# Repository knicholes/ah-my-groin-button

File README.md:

# Ah! My Groin!

A big red arcade button in a 3D-printed box. Hit it, it plays a sound clip,
then it goes back to sleep drawing 150 µA — so a set of AA cells lasts months
rather than days.

This repo is the complete build: PCB design files, firmware, the parametric
case model, a bill of materials with the exact parts used, and a
step-by-step assembly guide written for someone who has not done much
soldering.

---

## What to build

Two things have version numbers and they move independently:

| | Current | Where |
|---|---|---|
| **Board** | v3.2 | `kicad/` |
| **Case** | v2 — 120 × 120 × 140 mm | `case/v2-120x120x140/` |

Everything else in the repo (`ah-my-groin/`, `v2/README.md`'s v1 comparisons,
`case/v1-200x130x110/`) is earlier work kept for reference. You do not need it.

### Honest status

Read this before you spend money.

| Part | State |
|---|---|
| Firmware | **Proven.** Runs on a physically built board. 0.15 mA idle measured 2026-07-25. |
| Power design | **Proven.** The phantom-power drain that made an earlier build useless was found and fixed; idle went 14.44 mA → 0.15 mA. |
| v3.2 PCB | **Designed, not yet fabricated.** Passes `kicad/verify_v3.py`. Nobody has held one of these boards. |
| v2 case | **Designed, not yet printed.** Passes its clearance checks. Nobody has printed one. |

So: the electronics are known to work, but *this specific board revision and
this specific case* are unbuilt. If you build first, you are the pilot. The
verification scripts below exist precisely because earlier revisions shipped
with bugs that KiCad's own DRC passed cleanly.

---

## Specifications

| | |
|---|---|
| Idle current | ~150 µA (0.15 mA measured) |
| Playback current | ~150 mA |
| Power | 3 × AA, 2.4–3.3 V, master switch on the holder |
| Response | ~1 s from press to audio (the audio module's genuine cold-boot time) |
| Audio | DY-SV17F, 4 MB onboard flash, no SD card |
| MCU | Pro Mini 3.3 V / 8 MHz, deep sleep + INT0 wake |
| Board | 90 × 70 mm, 2.0 mm FR4, 2-layer |
| Case | 120 × 120 × 140 mm, all corners and edges rounded |
| Cost | roughly $60–90 depending on what you already own |

---

## Build it

Six stages. Each one points at the document that is authoritative for it —
this README only orients you.

### 1. Order the parts

**[`v2/bom.md`](v2/bom.md)** lists every component with the exact ASIN that
was purchased, plus what each one is for and which ones have gotchas (the Pro
Mini crystal must read 8.000, not 16.000).

### 2. Order the PCB

Gerbers come from `kicad/`. Send to JLCPCB or equivalent: **2 layers,
2.0 mm thickness** (not the default 1.6 — the extra stiffness is deliberate,
an earlier unit failed by flexing on impact).

**Before you order, run the two gates:**

```
"K:\Program Files\KiCad\10.0\bin\python.exe" kicad\verify_v3.py   # must print PASS
"K:\Program Files\KiCad\10.0\bin\python.exe" kicad\fitcheck_v3.py # then print it at 100%
```

`verify_v3.py` checks two classes of bug KiCad's DRC structurally cannot see:
parts buried under a module's overhanging body, and electrical intent
(transistor orientation, pull-downs, the phantom-power split). Every board
revision so far shipped with at least one of these and a clean DRC.

`fitcheck_v3.py` produces a 1:1 sheet. Print it at 100 %, **check the two
100 mm calibration bars with a ruler**, then lay the real DY-SV17F and Pro
Mini on their footprints. This takes five minutes and is the only thing that
catches a wrong footprint pitch. The calibration bars are there because a
printer once silently rescaled the sheet and produced a convincing false
alarm.

### 3. Solder the board

**[`SOLDERING_GUIDE.md`](SOLDERING_GUIDE.md)** — the long one. Twelve steps
from bare PCB to finished unit, written for a beginner: which end of the
resistor, how to hold the iron, how to put a multimeter in series without
shorting the battery pack. It includes the continuity checks to run before
first power-on and the measurements that prove the power design is working.

No wires are soldered anywhere. Every connection is a PCB trace — that was
the entire point of the v3.2 respin.

### 4. Flash the firmware

```
cd v2/firmware
pio run              # build
pio run -t upload    # upload via FTDI cable on the 6-pin header
pio device monitor   # 9600 baud
```

[PlatformIO](https://platformio.org/) handles the toolchain. The firmware is
~60 lines with no libraries — the audio module is driven by one GPIO pulse.
See [`v2/firmware/main.cpp`](v2/firmware/main.cpp); its header comment
documents the pin map and, more usefully, *why* three of the pins are the way
they are. Those three comments are each a bug that cost a debugging session.

### 5. Load the audio

The DY-SV17F appears as a USB mass-storage device. Copy a single MP3 named
`00001.mp3` to it. That is all.

**This repo ships no audio files.** The clip the project is named after is
copyrighted, so supply your own — record something, or use a clip you have
the right to use. Any MP3 works.

### 6. Print and assemble the case

STLs are in **[`case/v2-120x120x140/`](case/v2-120x120x140/)**, and that
folder's `README.md` has per-part print orientations and the constraints that
shaped the design. Three parts: `body.stl` ×1, `bottom.stl` ×1, `foot.stl`
**×4**.

0.4 mm nozzle, 0.2 mm layer, 20 % infill, PLA or PETG. **Check the size your
slicer reports** — `body.stl` must load as 120 × 120 × 140 mm.

Assembly is Step 12 of the soldering guide. Order matters: the speaker's
screws become unreachable once the PCB is mounted.

---

## Repo map

```
README.md              you are here
SOLDERING_GUIDE.md     the build, end to end — the main document
PINOUTS.md             pin and net reference for the board
PLANS.md               the format the guide is written in

kicad/                 v3.2 board — schematic, layout, gerbers
    build_v3.py        generates the board from source
    verify_v3.py       pre-fabrication gate — must PASS before ordering
    fitcheck_v3.py     generates the 1:1 footprint check sheet

v2/
    bom.md             bill of materials — the source of truth for parts
    README.md          why v2's architecture replaced v1's
    firmware/          PlatformIO project; main.cpp is the whole program

case/
    build_v2.py        generates the current case
    render_v2.py       preview renders
    v2-120x120x140/    STLs to print, plus README with print orientations
    build_case.py      generates the older wide case
    v1-200x130x110/    superseded, kept so it still reproduces

ah-my-groin/           v1 firmware (DFPlayer + SD card). Superseded.
```

## Regenerating things

Both the board and the case are generated from scripts, not hand-drawn — so
if you change a dimension, re-run the script rather than editing the output.

```
"K:\Program Files\KiCad\10.0\bin\python.exe" kicad\build_v3.py
"K:\...\blender.exe" --background --python case\build_v2.py
```

The case script refuses to finish if its clearance checks fail, if the button
notches got filled back in by a later boolean, or if the exported STL is not
in millimetres. All three of those are real bugs that happened and shipped
silently.

## Building a different case

Change `W, D, H` and `VERSION` at the top of `case/build_v2.py` and re-run —
outputs land in a new `case/<VERSION>/` folder and the old one is untouched.
The clearance checks will tell you what stopped fitting. Three constraints
are worth knowing before you start, all documented in the v2 case README:
the PCB cannot sit on posts rising straight from the tray, everything
tray-mounted has to pass up through the bottom opening, and the top rim
rounding is what limits the button flange.

## Contributing

Issues and pull requests welcome. If you build one, the most useful thing you
can report is anything in the "not yet fabricated / not yet printed" rows
above turning out wrong.

## License

MIT — see [`LICENSE`](LICENSE). Build it, sell it, modify it, no permission
needed; just keep the copyright notice.

That covers everything in this repo: firmware, the board design, the case
models, and the documentation. It does **not** cover any audio you load onto
the device — no audio ships here, and whatever you add is yours to clear.

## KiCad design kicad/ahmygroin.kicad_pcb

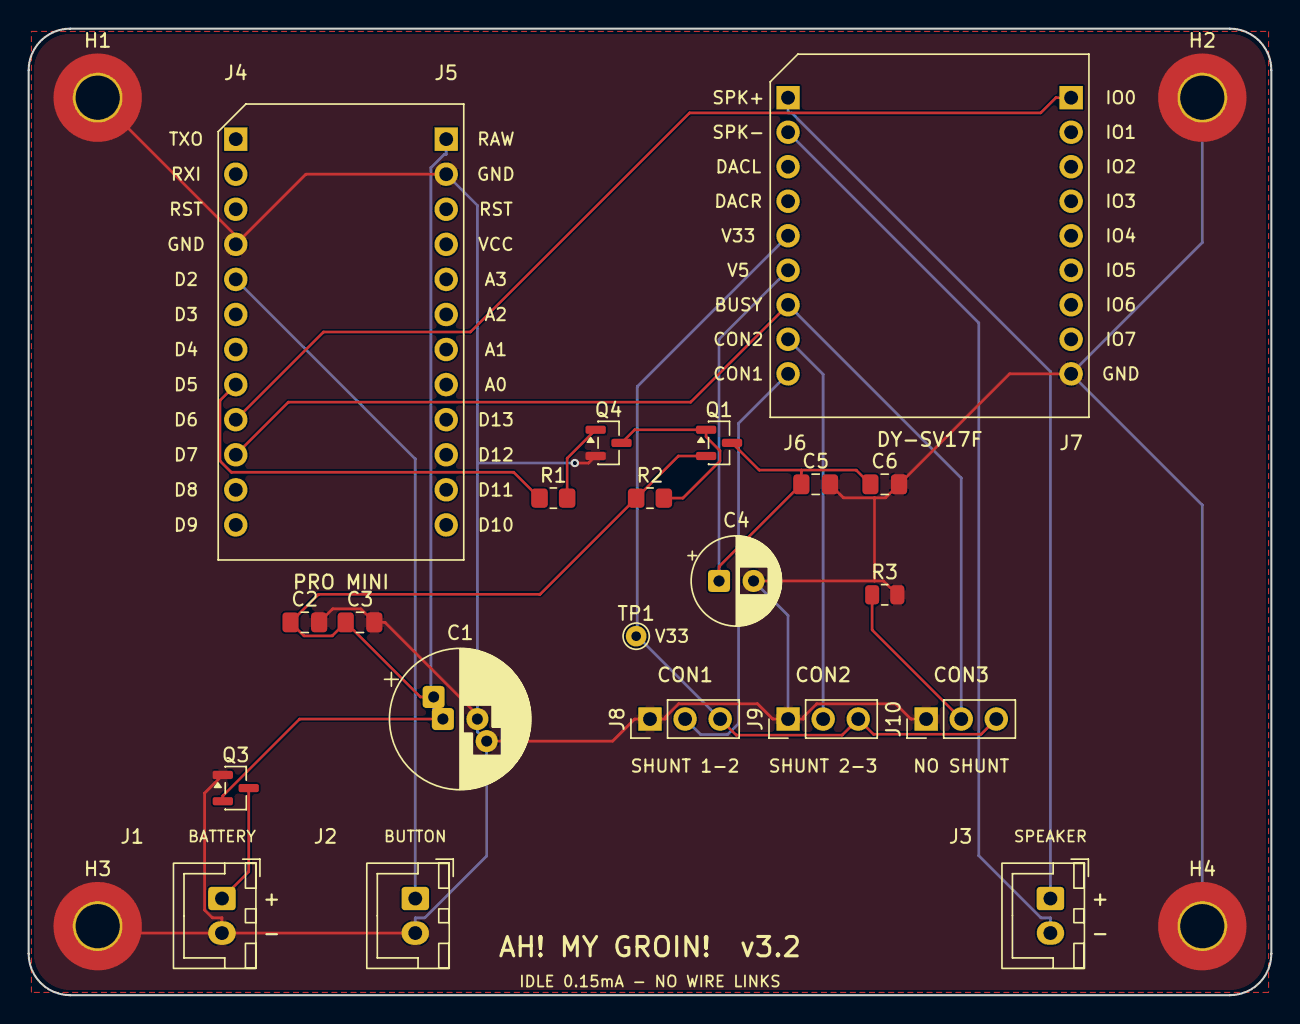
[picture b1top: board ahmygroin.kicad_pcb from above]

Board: 2 copper layers, 90.0 x 70.0 mm, 27 parts (0 on the bottom side), 15 nets.

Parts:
C1: 1000uF; CP_Radial_D10.0mm_P2.50mm_P5.00mm
C2, C6: 10uF; C_0805_2012Metric_Pad1.18x1.45mm_HandSolder
C3, C5: 0.1uF; C_0805_2012Metric_Pad1.18x1.45mm_HandSolder
C4: 100uF; CP_Radial_D6.3mm_P2.50mm
H1, H2, H3, H4: MountingHole; MountingHole_3.2mm_M3_Pad_TopBottom
J1: BAT; JST_XH_B2B-XH-A_1x02_P2.50mm_Vertical
J2: BTN; JST_XH_B2B-XH-A_1x02_P2.50mm_Vertical
J3: SPK; JST_XH_B2B-XH-A_1x02_P2.50mm_Vertical
J4: PROMINI_L; PinHeader_1x12_P2.54mm_Vertical
J5: PROMINI_R; PinHeader_1x12_P2.54mm_Vertical
J6: SV17F_IO; PinHeader_1x09_P2.54mm_Vertical
J7: SV17F_PWR; PinHeader_1x09_P2.54mm_Vertical
J8: MODE_CON1; PinHeader_1x03_P2.54mm_Vertical
J9: MODE_CON2; PinHeader_1x03_P2.54mm_Vertical
J10: MODE_CON3; PinHeader_1x03_P2.54mm_Vertical
Q1, Q3: AO3401A; SOT-23
Q4: MMBT3904; SOT-23
R1: 10k; R_0805_2012Metric_Pad1.20x1.40mm_HandSolder
R2: 100k; R_0805_2012Metric_Pad1.20x1.40mm_HandSolder
R3: 10k; R_0805_2012Metric
TP1: V33; TestPoint_THTPad_D1.5mm_Drill0.7mm

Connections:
/BTN_IN: J2.1, J4.5
/BUSY_IN: J4.10, J6.7, J10.2, R3.1
/CON1: J6.9, J8.2
/CON2: J6.8, J9.2
/GATE_CTRL: J4.8, R1.1
/GND: C1.2, C2.2, C3.2, C4.2, C5.2, C6.2, H1.1, H2.1, H3.1, H4.1, J1.2, J2.2, J4.4, J5.2, J7.9, J8.1, J9.1, J10.1, Q3.1, Q4.2, R3.2
/Q1_GATE: Q1.1, Q4.3, R2.2
/Q4_BASE: Q4.1, R1.2
/SPK_N: J3.2, J6.2
/SPK_P: J3.1, J6.1
/TRIG_OUT: J4.9, J7.1
/V33: J6.5, J8.3, J9.3, J10.3, TP1.1
/VBATT: J1.1, Q3.3
/VDFP: C4.1, C5.1, C6.1, J6.6, Q1.3
/VSYS: C1.1, C2.1, C3.1, J5.1, Q1.2, Q3.2, R2.1

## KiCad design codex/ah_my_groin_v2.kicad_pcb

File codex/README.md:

# Ah My Groin v2 KiCad Board

This folder contains a generated KiCad 10 first-pass PCB for the v2 board described in `../v2/README.md`.

Files:

- `ah_my_groin_v2.kicad_pro` - KiCad project
- `ah_my_groin_v2.kicad_pcb` - PCB layout
- `ah_my_groin_v2.kicad_sch` - companion schematic file
- `generate_v2_board.py` - deterministic board generator
- `drc.json` - latest KiCad CLI DRC report

Regenerate the PCB with KiCad's bundled Python:

```powershell
& 'K:\Program Files\KiCad\10.0\bin\python.exe' .\generate_v2_board.py
```

Run DRC:

```powershell
& 'K:\Program Files\KiCad\10.0\bin\kicad-cli.exe' pcb drc --format json --output '.\drc.json' '.\ah_my_groin_v2.kicad_pcb'
```

Current validation: 0 DRC violations and 0 unconnected items.

Layer note: only `F.SilkS` / `B.SilkS` silkscreen graphics are printed on the board. `F.Fab`, `B.Fab`, `Cmts.User`, `Dwgs.User`, hidden footprint properties, ratsnest lines, and selection/highlight graphics are KiCad editor aids unless they are explicitly included in a plot/export job. The generator keeps the manufactured silkscreen intentionally sparse, but restores useful component/test-point labels on `F.Fab` and assembly notes on `Cmts.User` so they remain visible in KiCad without overlapping pads or creating silkscreen DRC errors.

C6 uses the same generated 0805-style two-pad footprint as C2/C3/C5: 1.8 mm pad-center pitch with 0.85 mm wide pads, leaving about 0.95 mm copper-to-copper pad gap before solder mask expansion. KiCad DRC reports no clearance issue there.

U1 models the HiLetgo Pro Mini 3.3 V / 8 MHz module with the two 1x12 side headers, the top auxiliary pads `GND`, `A6`, `A7`, `DTR`, `TXO`, `RXI`, `VCC`, `GND`, `GND`, and the inner `A4` / `A5` pads. Only `RAW`, the required side-header signals, and the extra `GND` pads are connected by this v2 board; the other auxiliary pads are present for fit/orientation accuracy and left NC.

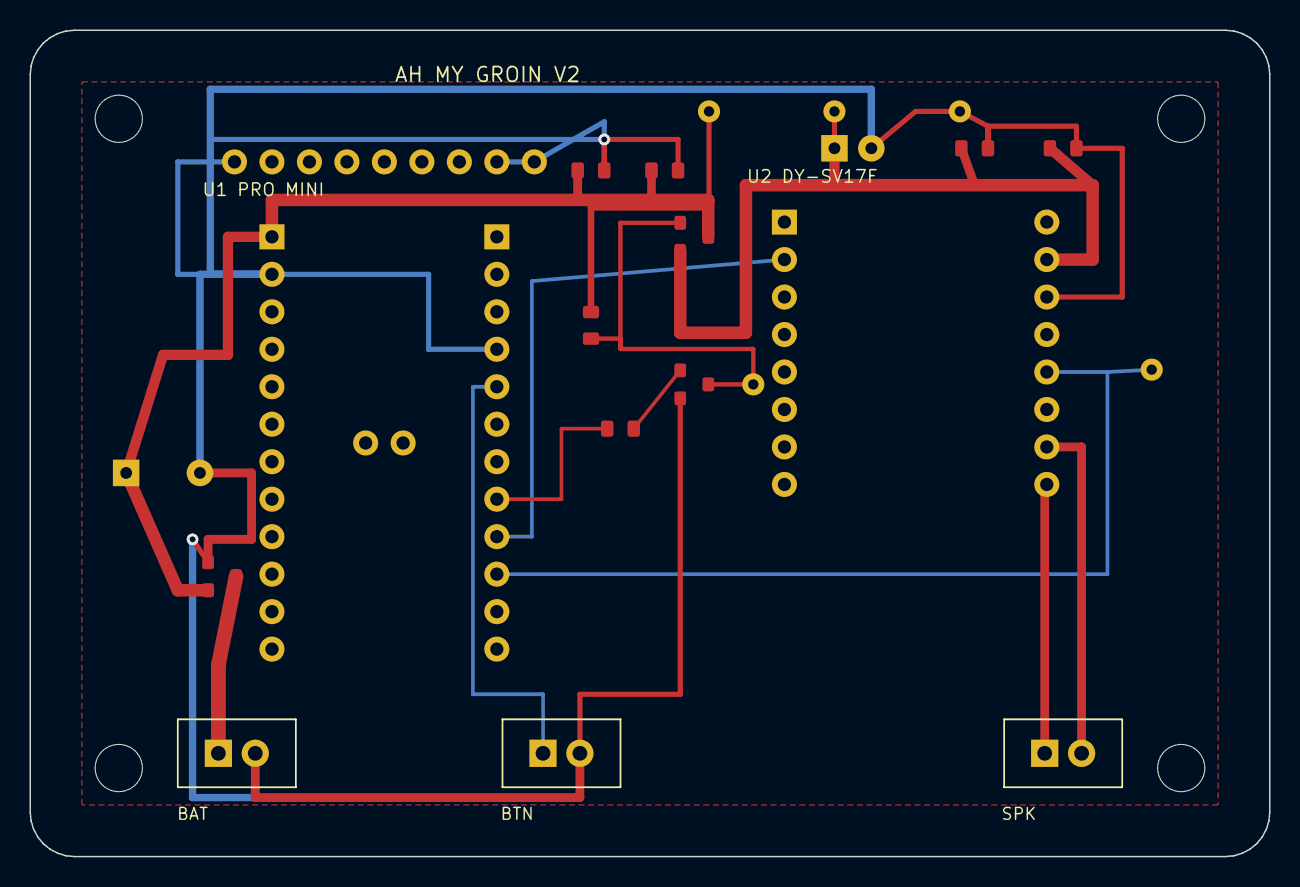
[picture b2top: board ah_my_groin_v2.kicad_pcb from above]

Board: 2 copper layers, 84.0 x 56.0 mm, 25 parts (0 on the bottom side), 12 nets.

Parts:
C1: 1000uF
C2, C6: 10uF
C3, C5: 0.1uF
C4: 100uF
H1, H2, H3, H4: M3 mount
J1: BAT + -
J2: BUTTON
J3: SPEAKER
Q1: AO3401A audio high-side
Q3: AO3401A reverse polarity
Q4: MMBT3904 gate pull-down
R1: 10k
R2: 100k
TP1: TP VSYS
TP2: TP VDFP
TP3: TP PFET_GATE
TP4: TP BUSY_IN
TP5: TP GND
U1: HiLetgo Pro Mini 3.3V/8MHz
U2: DY-SV17F audio module

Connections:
BTN_IN: J2.1, U1.R5
BUSY_IN: TP4.1, U1.R10, U2.12
GATE_CTRL: R1.1, U1.R8
GND: C1.2, C2.2, C3.2, C4.2, C5.2, C6.2, J1.2, J2.2, Q3.1, Q4.2, TP5.1, U1.L2, U1.R4, U1.T1, U1.T8, U1.T9, U2.14
PFET_GATE: Q1.1, Q4.3, R2.2, TP3.1
Q4_BASE: Q4.1, R1.2
SPK+: J3.1, U2.9
SPK-: J3.2, U2.10
TRIG_OUT: U1.R9, U2.2
VBATT: J1.1, Q3.3
VDFP: C4.1, C5.1, C6.1, Q1.2, TP2.1, U2.15
VSYS: C1.1, C2.1, C3.1, Q1.3, Q3.2, R2.1, TP1.1, U1.L1

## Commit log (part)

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2025-07-12 Things are almost working
2025-07-19 Things kind of work. About to experiment using different versions of code.
2026-05-16 Before cleaning everything up
